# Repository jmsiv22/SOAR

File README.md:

## ESP-Drone

### Introduction

**ESP-Drone** is an open source solution based on Espressif ESP32/ESP32-S2/ESP32-S3 Wi-Fi chip, which can be controlled by a mobile APP or gamepad over **Wi-Fi** connection. ESP-Drone comes with **simple hardware**, **clear and extensible code architecture**, and therefore this project can be used in **STEAM education** and other fields. The main code is ported from **Crazyflie** open source project with **GPL3.0** protocol.

> Currently support ESP32、ESP32S2、ESP32S3, please using ESP-IDF [release/v4.4](https://docs.espressif.com/projects/esp-idf/en/release-v4.4/esp32s2/get-started/index.html) branch as your develop environment

For more information, please check the sections below:
* **Getting Started**: [Getting Started](https://docs.espressif.com/projects/espressif-esp-drone/zh_CN/latest/gettingstarted.html)
* **Hardware Schematic**：[Hardware](https://docs.espressif.com/projects/espressif-esp-drone/zh_CN/latest/_static/ESP32_S2_Drone_V1_2/SCH_Mainboard_ESP32_S2_Drone_V1_2.pdf)
* **iOS APP Source code**: [ESP-Drone-iOS](https://github.com/EspressifApps/ESP-Drone-iOS)
* **Android APP Source code**: [ESP-Drone-Android](https://github.com/EspressifApps/ESP-Drone-Android)

### Features

1. Stabilize Mode
2. Height-hold Mode
3. Position-hold Mode
4. APP Control
5. cfclient Supported, refer https://github.com/leeebo/crazyflie-clients-python
6. ESP-BOX3 Joystick Control (through esp-now)

Note: to implement Height-hold/Position-hold mode, extension boards are needed. For more information, see Hardware Reference. 

### Third Party Copyrighted Code

Additional third party copyrighted code is included under the following licenses.

| Component | License | Origin |Commit ID |
| :---:  | :---: | :---: |:---: |
| core/crazyflie | GPL3.0  |[Crazyflie](https://github.com/bitcraze/crazyflie-firmware/tree/2021.01) |tag_2021_01 b448553|
| lib/dsp_lib |  | [esp32-lin](https://github.com/whyengineer/esp32-lin/tree/master/components/dsp_lib) |6fa39f4c|

### Support Policy

From December 2022, we will offer limited support on this project, but Pull Request is still welcomed!

### THANKS

1. Thanks to Bitcraze for the great [Crazyflie project](https://www.bitcraze.io/%20).
2. Thanks to Espressif for the powerful [ESP-IDF framework](https://docs.espressif.com/projects/esp-idf/en/latest/esp32s2/get-started/index.html).
3. Thanks to WhyEngineer for the useful [ESP-DSP lib](https://github.com/whyengineer/esp32-lin/tree/master/components/dsp_lib).

# S O A R
Modified by Senior Design group: John Shaw, Aiden Kempista, Ryan Weiss, Thomas Mullenberg

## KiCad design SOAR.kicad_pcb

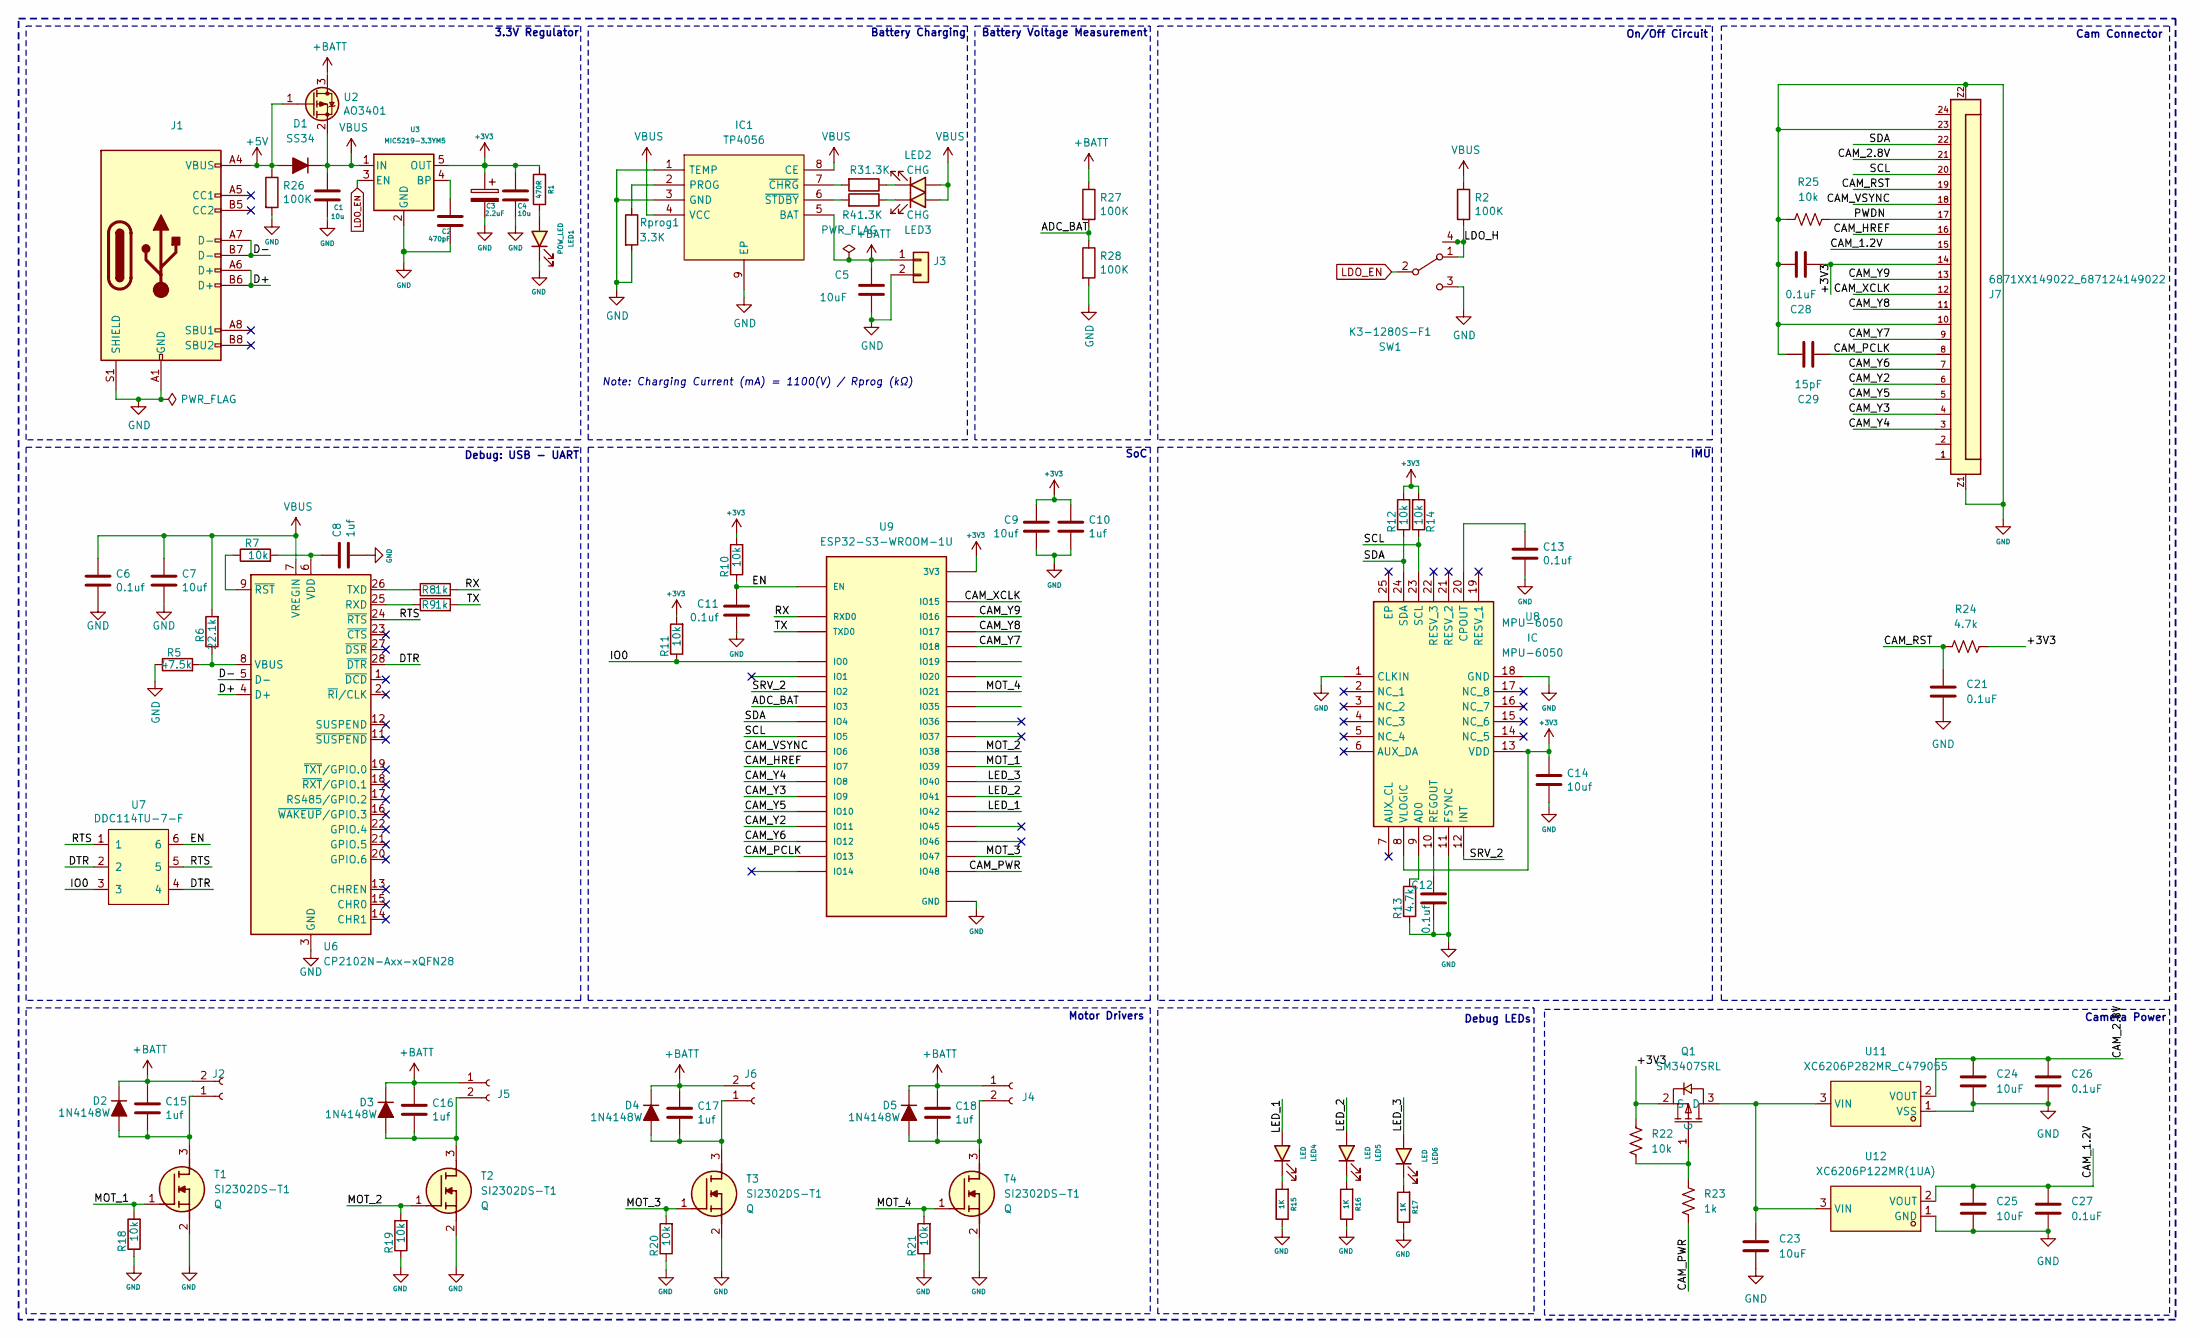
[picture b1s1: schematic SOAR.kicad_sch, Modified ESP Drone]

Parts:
C1, C4: 10u; C_0603_1608Metric
C2: 470pF; C_0603_1608Metric
C3: 2.2uF; C_0805_2012Metric
C5, C23, C24, C25: 10uF; C_0603_1608Metric
C6, C11, C12, C13: 0.1uf; C_0603_1608Metric
C7, C9, C14: 10uf; C_0603_1608Metric
C8, C10, C15, C16, C17, C18: 1uf; C_0603_1608Metric
C21, C26, C27, C28: 0.1uF; C_0603_1608Metric
C29: 15pF; C_0603_1608Metric
D1: SS34; D_SMA
D2, D3, D4, D5: 1N4148W; D_SOD-323
IC1: TP4056; SO08-PAD-300; Manufacturer_Part_Number TP4056-42-ESOP8
J1: USB_C_Receptacle_USB2.0; USB_C_Receptacle_HRO_TYPE-C-31-M-12
J2, J4, J5, J6: Conn_01x02_Female; JST_GH_SM02B-GHS-TB_1x02-1MP_P1.25mm_Horizontal
J3: B2B-PH-SM4-TB(LF)(SN); JST_PH_B2B-PH-SM4-TB_1x02-1MP_P2.00mm_Vertical
J7: 6871XX149022_687124149022; 687124149022; PART-NUMBER 687124149022
LED1: POW_LED; LED_0603_1608Metric
LED2, LED3: CHG; LED_0603_1608Metric
LED4, LED5, LED6: LED; LED_0603_1608Metric
Q1: SM3407SRL; SOT-23-3_L2.9-W1.6-P1.90-LS2.8-BR; LCSC Part C235545
R1: 470R; R_0603_1608Metric
R2, R26, R27, R28: 100K; R_0603_1608Metric
R3, R4: 1.3K; R_0603_1608Metric
R5: 47.5k; R_0603_1608Metric
R6: 22.1k; R_0603_1608Metric
R7, R10, R11, R12, R14, R18, R19, R20, R21, R22, R25: 10k; R_0603_1608Metric
R8, R9, R23: 1k; R_0603_1608Metric
R13, R24: 4.7k; R_0603_1608Metric
R15, R16, R17: 1K; R_0603_1608Metric
Rprog1: 3.3K; R_0603_1608Metric
SW1: K3-1280S-F1; SW-SMD_K3-1280S-K1
T1, T2, T3, T4: SI2302DS-T1; SOT-23-3_L2.9-W1.3-P1.90-LS2.4-BR; Mouser Part Number 781-SI2302DS
U2: AO3401; SOT-23
U3: MIC5219-3.3YM5; SOT-23-5
U6: CP2102N-Axx-xQFN28; QFN-28-1EP_5x5mm_P0.5mm_EP3.35x3.35mm
U7: DDC114TU-7-F; SOT-363_SC-70-6
U8: MPU-6050; InvenSense_QFN-24_4x4mm_P0.5mm_NoMask; Mouser Part Number 410-MPU-6050
U9: ESP32-S3-WROOM-1U; XCVR_ESP32-S3-WROOM-1U; PARTREV v0.6
U11: XC6206P282MR_C479055; SOT-23-3_L2.9-W1.6-P1.90-LS2.8-BR; LCSC Part C479055
U12: XC6206P122MR(1UA); SOT-23-3_L2.9-W1.6-P1.90-LS2.8-BR; LCSC Part C2827649

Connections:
+3V3: C3.1, C4.1, C9.1, C10.1, C14.1, C28.1, J7.14, Q1.2 (S), R1.2, R10.2, R11.2, R12.2, R14.2, R22.1, R24.2, U3.5 (OUT), U8.8 (VLOGIC), U8.13 (VDD), U9.2 (3V3)
+5V: D1.2 (A), J1.A4 (VBUS), J1.A9 (VBUS), J1.B4 (VBUS), J1.B9 (VBUS), R26.1, U2.1 (G)
+BATT: C5.1, C15.1, C16.1, C17.1, C18.1, D2.1 (K), D3.1 (K), D4.1 (K), D5.1 (K), IC1.5 (BAT), J2.2, J3.1, J4.1, J5.1, J6.2, R27.1, U2.3 (D)
/ADC_BAT: R27.2, R28.1, U9.15 (IO3)
/CAM_1.2V: C25.1, C27.1, J7.15, U12.2 (VOUT)
/CAM_2.8V: C24.1, C26.1, J7.21, U11.2 (VOUT)
/CAM_HREF: J7.16, U9.7 (IO7)
/CAM_PCLK: C29.1, J7.8, U9.21 (IO13)
/CAM_PWR: R23.2, U9.25 (IO48)
/CAM_RST: C21.2, J7.19, R24.1
/CAM_VSYNC: J7.18, U9.6 (IO6)
/CAM_XCLK: J7.12, U9.8 (IO15)
/CAM_Y2: J7.6, U9.19 (IO11)
/CAM_Y3: J7.4, U9.17 (IO9)
/CAM_Y4: J7.3, U9.12 (IO8)
/CAM_Y5: J7.5, U9.18 (IO10)
/CAM_Y6: J7.7, U9.20 (IO12)
/CAM_Y7: J7.9, U9.11 (IO18)
/CAM_Y8: J7.11, U9.10 (IO17)
/CAM_Y9: J7.13, U9.9 (IO16)
/D+: J1.A6 (D+), J1.B6 (D+), U6.4 (D+)
/D-: J1.A7 (D-), J1.B7 (D-), U6.5 (D-)
/DTR: U6.28 (~DTR), U7.2, U7.4
/EN: C11.1, R10.1, U7.6, U9.3 (EN)
/IO0: R11.1, U7.3, U9.27 (IO0)
/LDO_H: R2.2, SW1.1 (A), SW1.4
/LED_1: LED4.2 (A), U9.35 (IO42)
/LED_2: LED5.2 (A), U9.34 (IO41)
/LED_3: LED6.2 (A), U9.33 (IO40)
/MOT_1: R18.2, T1.1 (G), U9.32 (IO39)
/MOT_2: R19.2, T2.1 (G), U9.31 (IO38)
/MOT_3: R20.2, T3.1 (G), U9.24 (IO47)
/MOT_4: R21.2, T4.1 (G), U9.23 (IO21)
/PWDN: J7.17, R25.1
/RTS: U6.24 (~RTS), U7.1, U7.5
/RX: R8.2, U9.36 (RXD0)
/SCL: J7.20, R14.1, U8.23 (SCL), U9.5 (IO5)
/SDA: J7.22, R12.1, U8.24 (SDA), U9.4 (IO4)
/SRV_2: U8.12 (INT), U9.38 (IO2)
/TX: R9.2, U9.37 (TXD0)
GND: C1.2, C2.2, C3.2, C4.2, C5.2, C6.2, C7.2, C8.2, C9.2, C10.2, C11.2, C12.2, C13.2, C14.2, C21.1, C23.2, C24.2, C25.2, C26.2, C27.2, C28.2, C29.2, IC1.1 (TEMP), IC1.3 (GND), IC1.9 (EP), J1.A1 (GND), J1.A12 (GND), J1.B1 (GND), J1.B12 (GND), J1.S1 (SHIELD), J3.2, J7.10, J7.23, J7.Z1, J7.Z2, LED1.1 (K), R5.1, R13.1, R15.1, R16.1, R17.1, R18.1, R19.1, R20.1, R21.1, R25.2, R26.2, R28.2, Rprog1.2, SW1.3 (C), T1.2 (S), T2.2 (S), T3.2 (S), T4.2 (S), U3.2 (GND), U6.3 (GND), U6.29 (GND), U8.1 (CLKIN), U8.11 (FSYNC), U8.18 (GND), U9.1 (GND), U9.40 (GND), U9.41_1 (GND), U9.41_2 (GND), U9.41_3 (GND), U9.41_4 (GND), U9.41_5 (GND), U9.41_6 (GND), U9.41_7 (GND), U9.41_8 (GND), U9.41_9 (GND), U11.1 (VSS), U12.1 (GND)
LDO_EN: SW1.2 (B), U3.3 (EN)
unnamed: C15.2, D2.2 (A), J2.1, T1.3 (D)
unnamed: C16.2, D3.2 (A), J5.2, T2.3 (D)
unnamed: C17.2, D4.2 (A), J6.1, T3.3 (D)
unnamed: C18.2, D5.2 (A), J4.2, T4.3 (D)
unnamed: IC1.2 (PROG), Rprog1.1
unnamed: IC1.7 (~CHRG), R3.2
unnamed: IC1.6 (~STDBY), R4.2
unnamed: LED1.2 (A), R1.1
unnamed: LED2.1 (K), R3.1
unnamed: LED3.1 (K), R4.1
unnamed: LED4.1 (K), R15.2
unnamed: LED5.1 (K), R16.2
unnamed: LED6.1 (K), R17.2
unnamed: C23.1, Q1.3 (D), U11.3 (VIN), U12.3 (VIN)
unnamed: Q1.1 (G), R22.2, R23.1
unnamed: C2.1, U3.4 (BP)
unnamed: R9.1, U6.25 (RXD)
unnamed: R8.1, U6.26 (TXD)
unnamed: R5.2, R6.1, U6.8 (VBUS)
unnamed: C8.1, R7.2, U6.6 (VDD)
unnamed: R7.1, U6.9 (~RST)
unnamed: R13.2, U8.9 (AD0)
unnamed: C13.1, U8.20 (CPOUT)
unnamed: C12.1, U8.10 (REGOUT)
VBUS: C1.1, C6.1, C7.1, D1.1 (K), IC1.4 (VCC), IC1.8 (CE), LED2.2 (A), LED3.2 (A), R2.1, R6.2, U2.2 (S), U3.1 (IN), U6.7 (VREGIN)

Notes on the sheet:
SoC
Battery Voltage Measurement
IMU
Motor Drivers
Camera Power
Battery Charging
Debug LEDs
Debug: USB - UART
Cam Connector
3.3V Regulator
Note: Charging Current (mA) = 1100(V) / Rprog (kΩ)
On/Off Circuit

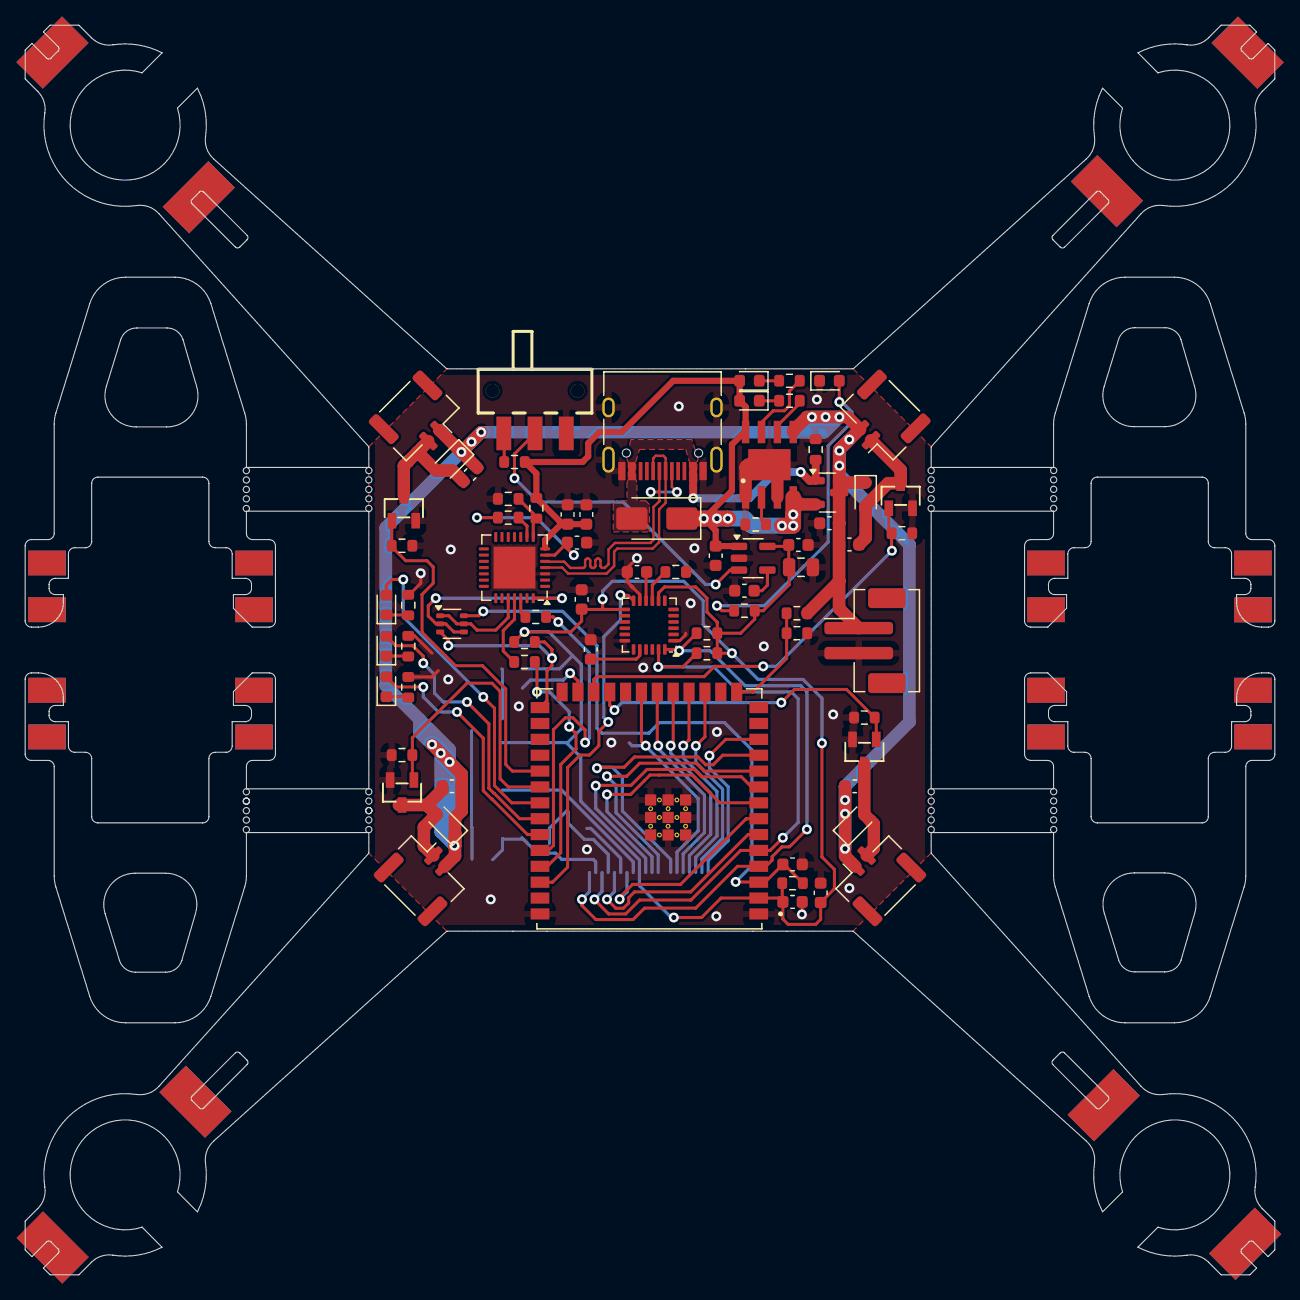
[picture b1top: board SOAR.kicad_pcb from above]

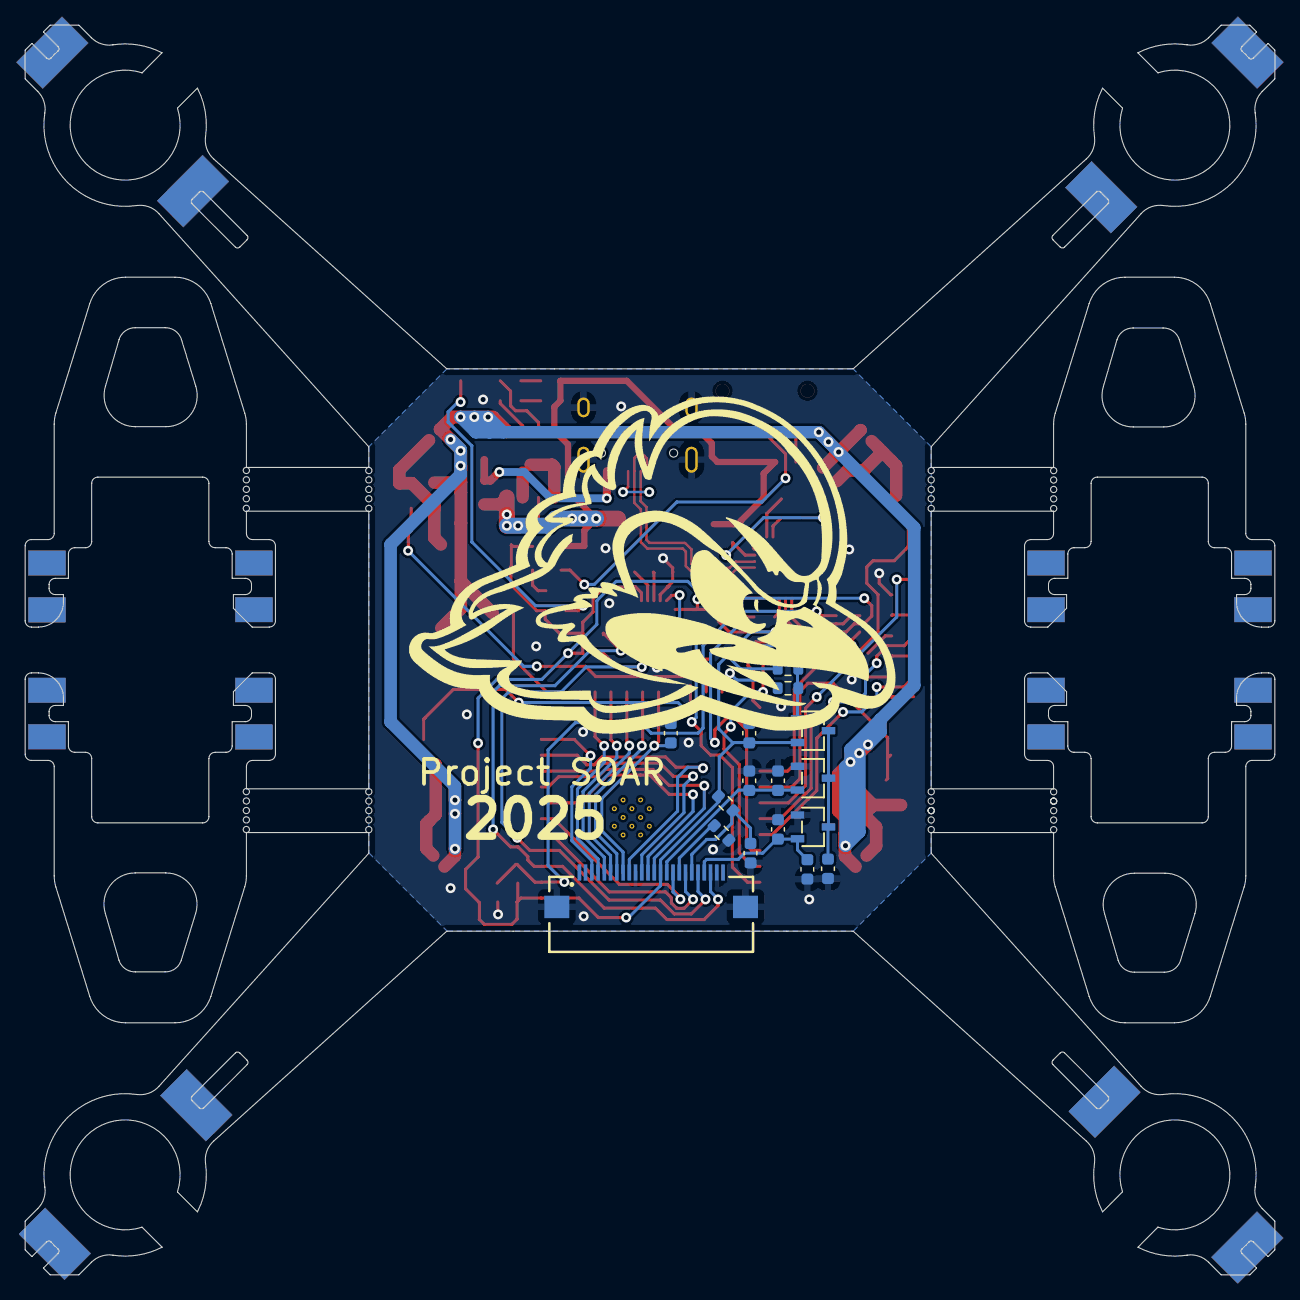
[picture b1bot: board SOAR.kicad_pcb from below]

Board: 2 copper layers, 100.0 x 100.0 mm, 96 parts (16 on the bottom side), 67 nets.

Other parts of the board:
mouse-bite-3mm-slot, mouse-bite-3mm-slot#2, mouse-bite-3mm-slot#3, mouse-bite-3mm-slot#4, mouse-bite-3mm-slot#5, mouse-bite-3mm-slot#6, mouse-bite-3mm-slot#7, mouse-bite-3mm-slot#8: VAL**; mouse-bite-3mm-slot_1

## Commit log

2025-04-24 fixed readme
2025-04-28 Fixed config issue.
2025-05-01 New code from official ESP drone.
2025-05-12 New File directory. Added python.
2025-05-12 Readme Added.
2025-05-12 Added python script
2025-05-12 Schematics Added
